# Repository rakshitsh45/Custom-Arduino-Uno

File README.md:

# Custom Arduino Uno PCB

A custom Arduino Uno compatible PCB designed using KiCad.

## Features
- ATmega328P-A microcontroller
- CH340G USB-to-Serial converter
- USB-A connector
- AMS1117 voltage regulator
- 16 MHz crystal oscillator
- ISP programming header
- Analog and digital headers

## Software Used
- KiCad

## Project Status
Completed PCB design with zero DRC errors and warnings.

## PCB Layout

## Schematic

## 3D View

## Author
Rakshit

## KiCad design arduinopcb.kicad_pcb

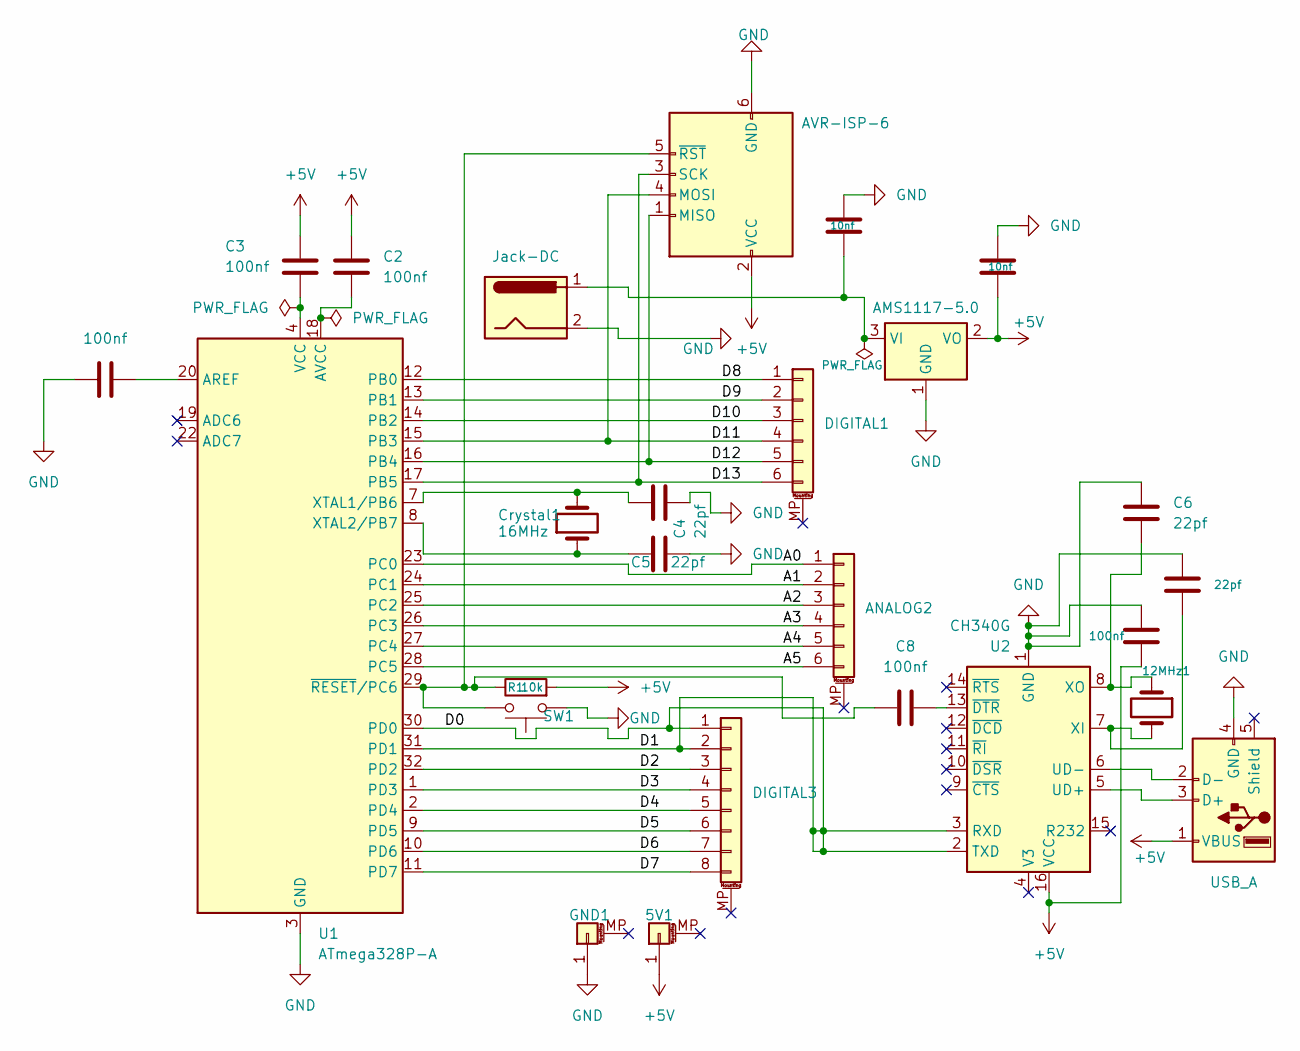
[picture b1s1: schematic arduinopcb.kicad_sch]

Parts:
5V1: PinHeader_1x01_P2.54mm_Horizontal
12MHz1: Crystal; Crystal_SMD_3225-4Pin_3.2x2.5mm
ANALOG2: PinHeader_1x06_P2.54mm_Vertical
C1, C2, C3, C8, C9: 100nf; C_0805_2012Metric
C4, C5, C6, C7: 22pf; C_0805_2012Metric
C11, C12: 10nf; C_1206_3216Metric
Crystal1: 16MHz; Crystal_SMD_3225-4Pin_3.2x2.5mm
DIGITAL1: PinHeader_1x06_P2.54mm_Vertical
DIGITAL3: PinHeader_1x08_P2.54mm_Vertical
GND1: PinHeader_1x01_P2.54mm_Horizontal
J1: USB_A; USB_A_Molex_67643_Horizontal
J2: Jack-DC; BarrelJack_Horizontal
J3: AVR-ISP-6; PinHeader_1x06_P2.54mm_Vertical
R1: 10k; R_0805_2012Metric
SW1: SW_Push; SW_PUSH_6mm
U1: ATmega328P-A; TQFP-32_7x7mm_P0.8mm
U2: CH340G; SOIC-16_3.9x9.9mm_P1.27mm
U3: AMS1117-5.0; SOT-223-3_TabPin2

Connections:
+5V: 5V1.1, C2.1, C3.1, C9.2, C11.2, J1.1 (VBUS), J3.2 (VCC), R1.2, U2.16 (VCC), U3.2 (VO)
/A0: ANALOG2.1, U1.23 (PC0)
/A1: ANALOG2.2, U1.24 (PC1)
/A2: ANALOG2.3, U1.25 (PC2)
/A3: ANALOG2.4, U1.26 (PC3)
/A4: ANALOG2.5, U1.27 (PC4)
/A5: ANALOG2.6, U1.28 (PC5)
/D0: DIGITAL3.1, DIGITAL3.2, U1.30 (PD0), U1.31 (PD1), U2.2 (TXD), U2.3 (RXD)
/D2: DIGITAL3.3, U1.32 (PD2)
/D3: DIGITAL3.4, U1.1 (PD3)
/D4: DIGITAL3.5, U1.2 (PD4)
/D5: DIGITAL3.6, U1.9 (PD5)
/D6: DIGITAL3.7, U1.10 (PD6)
/D7: DIGITAL3.8, U1.11 (PD7)
/D8: DIGITAL1.1, U1.12 (PB0)
/D9: DIGITAL1.2, U1.13 (PB1)
/D10: DIGITAL1.3, U1.14 (PB2)
/D11: DIGITAL1.4, J3.4 (MOSI), U1.15 (PB3)
/D12: DIGITAL1.5, J3.1 (MISO), U1.16 (PB4)
/D13: DIGITAL1.6, J3.3 (SCK), U1.17 (PB5)
GND: C1.1, C4.2, C5.2, C6.1, C7.1, C9.1, C11.1, C12.1, GND1.1, J1.4 (GND), J2.2, J3.6 (GND), SW1.1, U1.3 (GND), U1.5 (GND), U1.21 (GND), U2.1 (GND), U3.1 (GND)
unnamed: C3.2, U1.4 (VCC), U1.6 (VCC)
unnamed: J1.3 (D+), U2.5 (UD+)
unnamed: J1.2 (D-), U2.6 (UD-)
unnamed: C8.1, J3.5 (~RST), R1.1, SW1.2, U1.29 (~RESET/PC6)
unnamed: C1.2, U1.20 (AREF)
unnamed: C2.2, U1.18 (AVCC)
unnamed: C4.1, Crystal1.2, U1.7 (XTAL1/PB6)
unnamed: C5.1, Crystal1.1, U1.8 (XTAL2/PB7)
unnamed: 12MHz1.2, C7.2, U2.7 (XI)
unnamed: 12MHz1.1, C6.2, U2.8 (XO)
unnamed: C8.2, U2.13 (~DTR)
unnamed: C12.2, J2.1, U3.3 (VI)

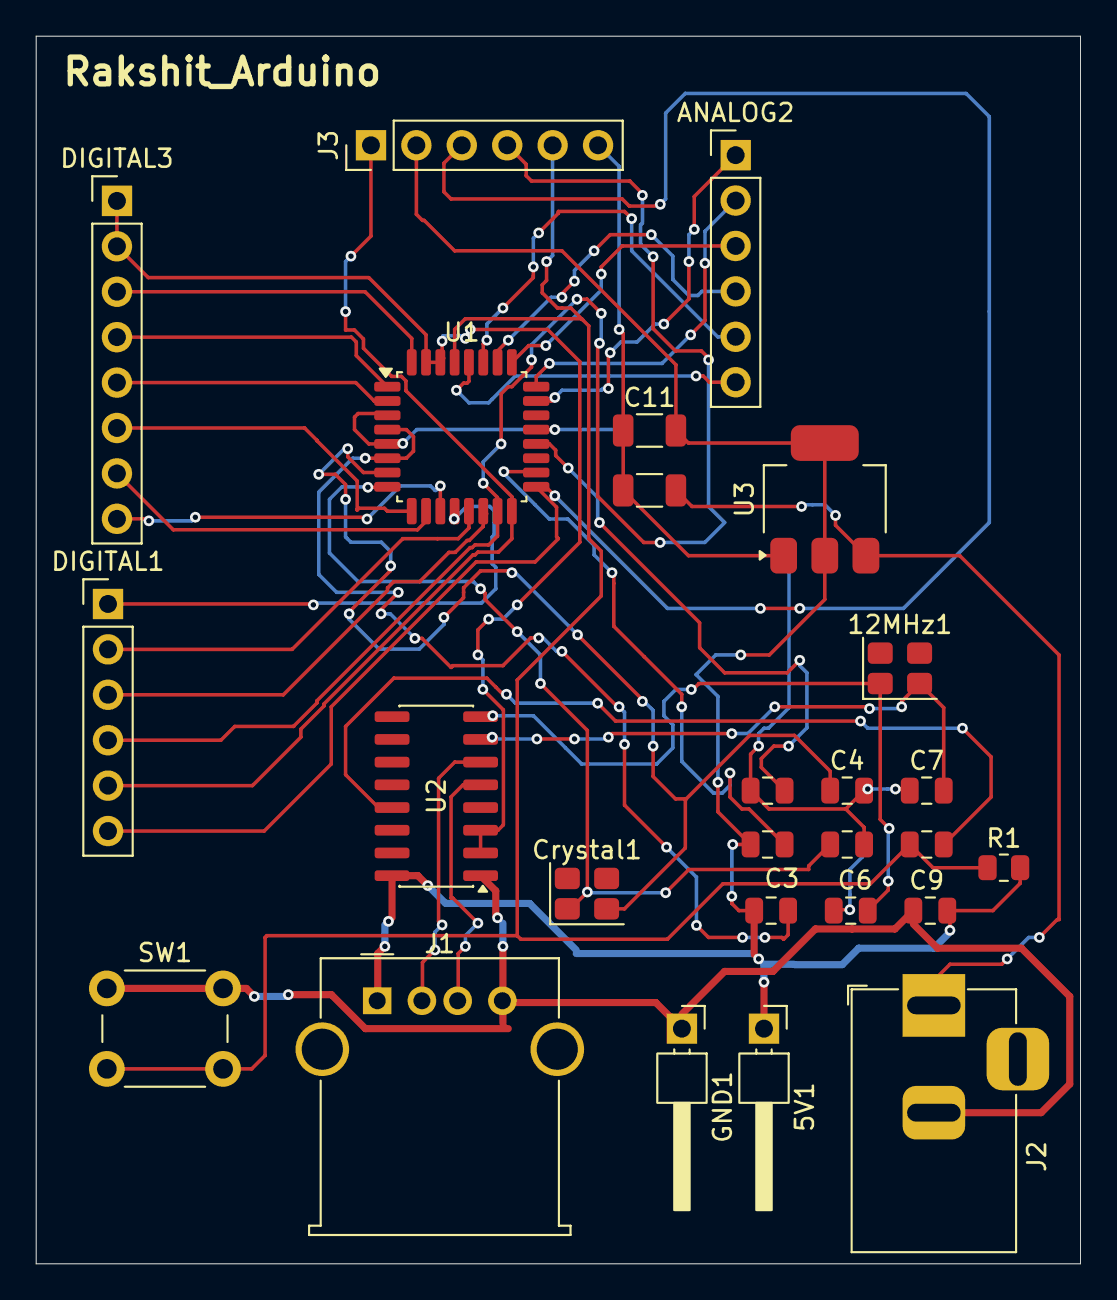
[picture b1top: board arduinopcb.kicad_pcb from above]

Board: 2 copper layers, 58.4 x 68.7 mm, 26 parts (0 on the bottom side), 33 nets.

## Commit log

2026-05-11 Initial upload of Arduino Uno PCB project
2026-05-11 Added PCB and schematic images
2026-05-11 Add MIT License to the project
